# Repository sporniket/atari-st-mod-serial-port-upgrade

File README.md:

# A serial port mod for the Atari ST

> [WARNING] Please read carefully this note before using this project. It contains important facts.

Content

1. What is **A serial port mod for the Atari ST**, and when to use it ?
2. What should you know before using **A serial port mod for the Atari ST** ?
3. How to use **A serial port mod for the Atari ST** ?
4. Known issues
5. Miscellanous

## 1. What is **A serial port mod for the Atari ST**, and when to use it ?

**A serial port mod for the Atari ST** is a mod that will allow an Atari ST computer with a DIP version of the MC68901 to double the maximum speed of the serial port. _The mod require some physical modification of the original computer, including **cutting a pin of the MC68901** !_

A description of the mod is available on the "ST Format" #71, a scan of the pages are provided for reference in this repository. 

### Licence

**A serial port mod for the Atari ST** is published under the Creative Commons CC0 license. You can find a copy of the licence there : https://creativecommons.org/publicdomain/zero/1.0/legalcode

You can copy, modify, distribute and perform the work, even for commercial purposes, all without asking permission.

**A serial port mod for the Atari ST** is distributed in the hope that it will be useful, but WITHOUT ANY WARRANTY; without even the implied warranty of MERCHANTABILITY or FITNESS FOR A PARTICULAR PURPOSE. 

### Release notes

> No releases yet

## 2. What should you know before using **A serial port mod for the Atari ST** ?

**A serial port mod for the Atari ST** is made using Kicad 5.

> Do not use **A serial port mod for the Atari ST** if this project is not suitable for your project.

## 3. How to use **A serial port mod for the Atari ST** ?

### From sources

To get the latest available work, one must clone the git repository.

	git clone https://github.com/sporniket/atari-st-mod-serial-port-upgrade.git

Then, open the project with Kicad 5

## 4. Known issues
See the [project issues](https://github.com/sporniket/atari-st-mod-serial-port-upgrade/issues) page.

## 5. Miscellanous

### The original description of the mod

* [page 1](./atari-st-format-issue-071_45.jpg)
* [page 2](./atari-st-format-issue-071_46.jpg)

### Report issues
Use the [project issues](https://github.com/sporniket/atari-st-mod-serial-port-upgrade/issues) page.

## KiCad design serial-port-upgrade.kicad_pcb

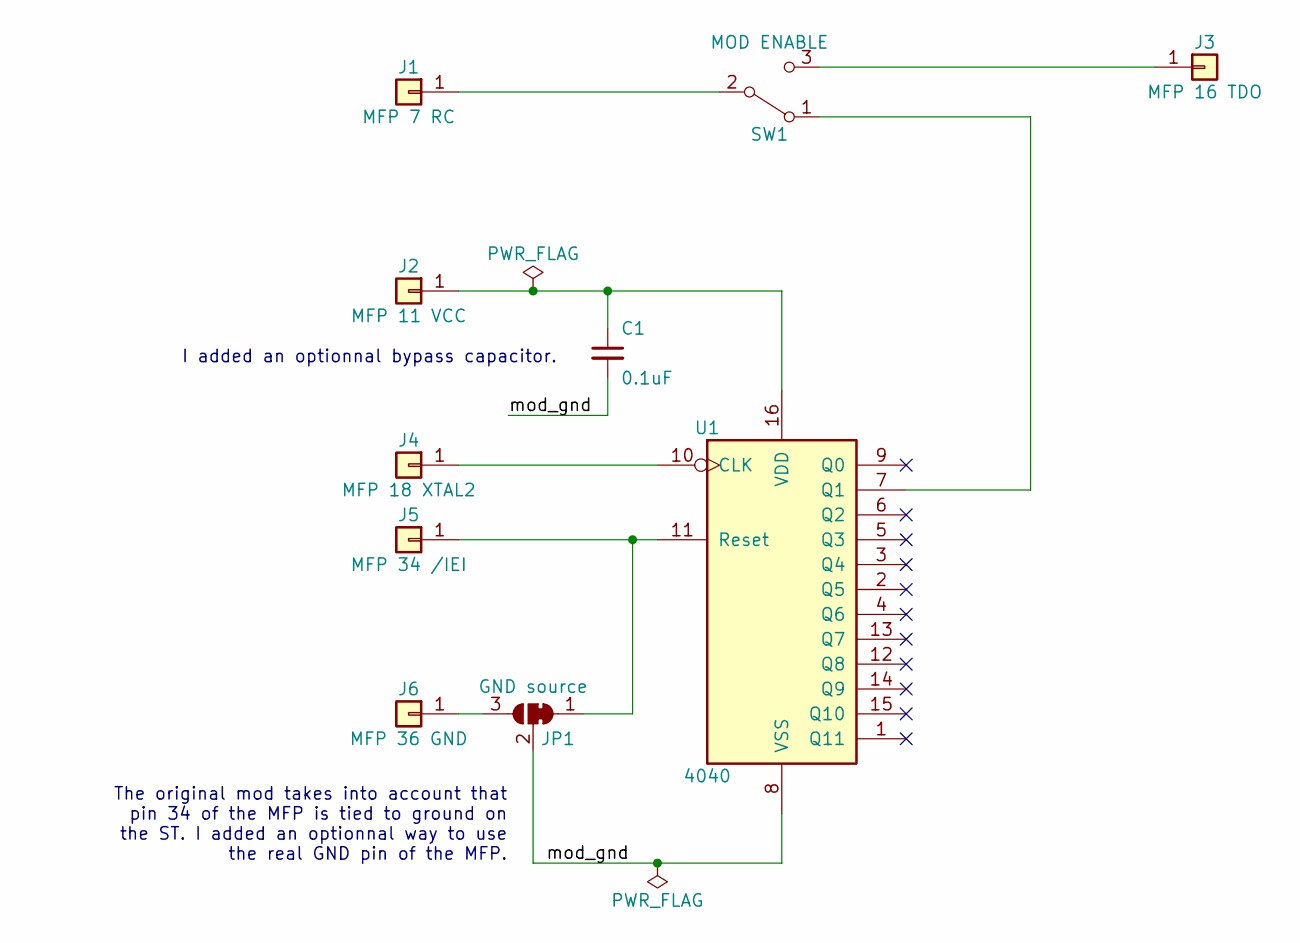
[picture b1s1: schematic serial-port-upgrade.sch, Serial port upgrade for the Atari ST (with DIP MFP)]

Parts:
C1: 0.1uF; Passive_THT_capacitor_W2.54mm_L10.16mm
J1: MFP 7 RC; PinHeader_1x01_P2.54mm_Vertical
J2: MFP 11 VCC; PinHeader_1x01_P2.54mm_Vertical
J3: MFP 16 TDO; PinHeader_1x01_P2.54mm_Vertical
J4: MFP 18 XTAL2; PinHeader_1x01_P2.54mm_Vertical
J5: MFP 34 /IEI; PinHeader_1x01_P2.54mm_Vertical
J6: MFP 36 GND; PinHeader_1x01_P2.54mm_Vertical
JP1: GND source; SolderJumper-3_P1.3mm_Bridged12_RoundedPad1.0x1.5mm
SW1: MOD ENABLE; PinHeader_1x03_P2.54mm_Horizontal
U1: 4040; DIP-16_W7.62mm_Socket_LongPads

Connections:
/mod_gnd: C1.2, JP1.2 (C), U1.8 (VSS)
unnamed: C1.1, J2.1, U1.16 (VDD)
unnamed: J1.1, SW1.2 (B)
unnamed: J3.1, SW1.3 (C)
unnamed: J4.1, U1.10 (CLK)
unnamed: J5.1, JP1.1 (A), U1.11 (Reset)
unnamed: J6.1, JP1.3 (B)
unnamed: SW1.1 (A), U1.7 (Q1)

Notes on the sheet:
The original mod takes into account that pin 34 of the MFP is tied to ground on the ST. I added an optionnal way to use the real GND pin of the MFP.
I added an optionnal bypass capacitor.

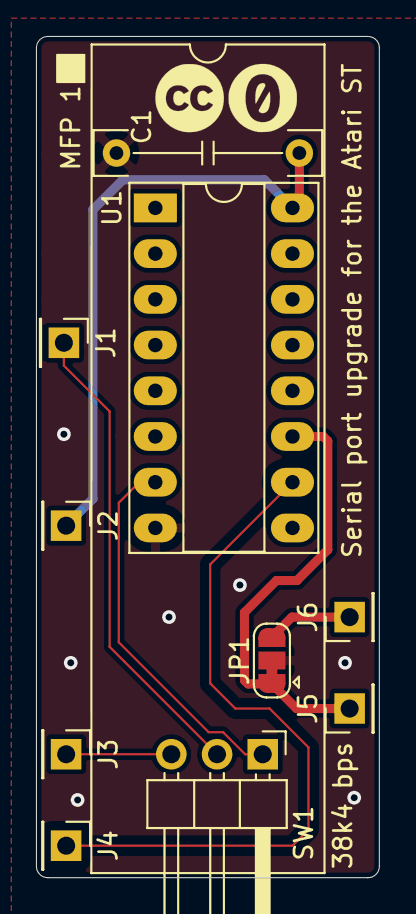
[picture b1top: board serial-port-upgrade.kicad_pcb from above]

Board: 2 copper layers, 19.0 x 46.7 mm, 10 parts (0 on the bottom side), 8 nets.

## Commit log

2022-11-04 initial commit of new project : replace README, add licence and reference description
2022-11-04 schematic convertion
2022-11-04 added some notes about my additions to the mod
2022-11-04 PCB done
2022-11-04 added some annotation
2022-11-04 update copper pours
2022-11-04 adjusted copper pour parameters
2022-11-04 latest details, gallery
